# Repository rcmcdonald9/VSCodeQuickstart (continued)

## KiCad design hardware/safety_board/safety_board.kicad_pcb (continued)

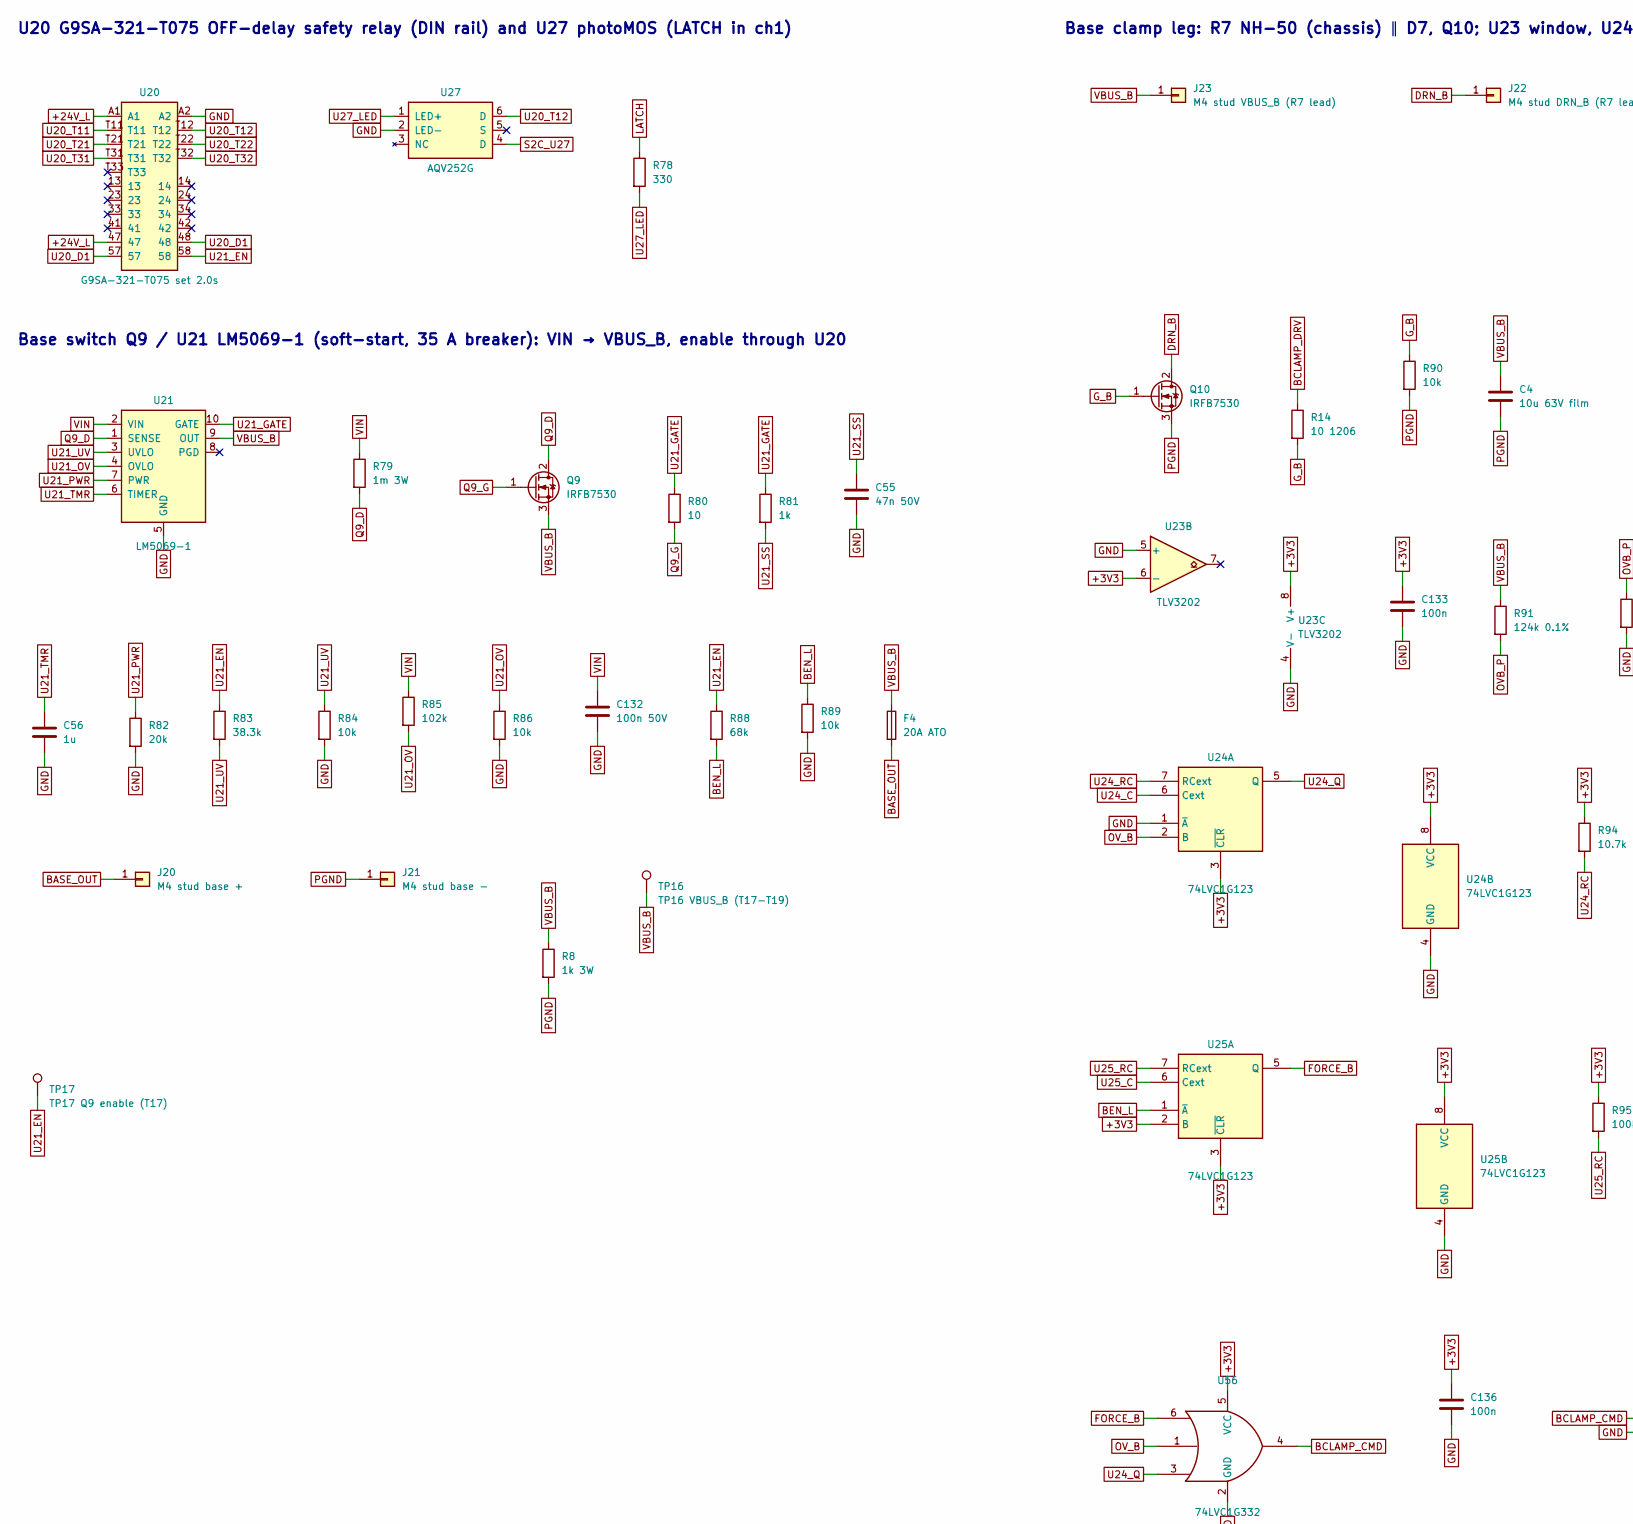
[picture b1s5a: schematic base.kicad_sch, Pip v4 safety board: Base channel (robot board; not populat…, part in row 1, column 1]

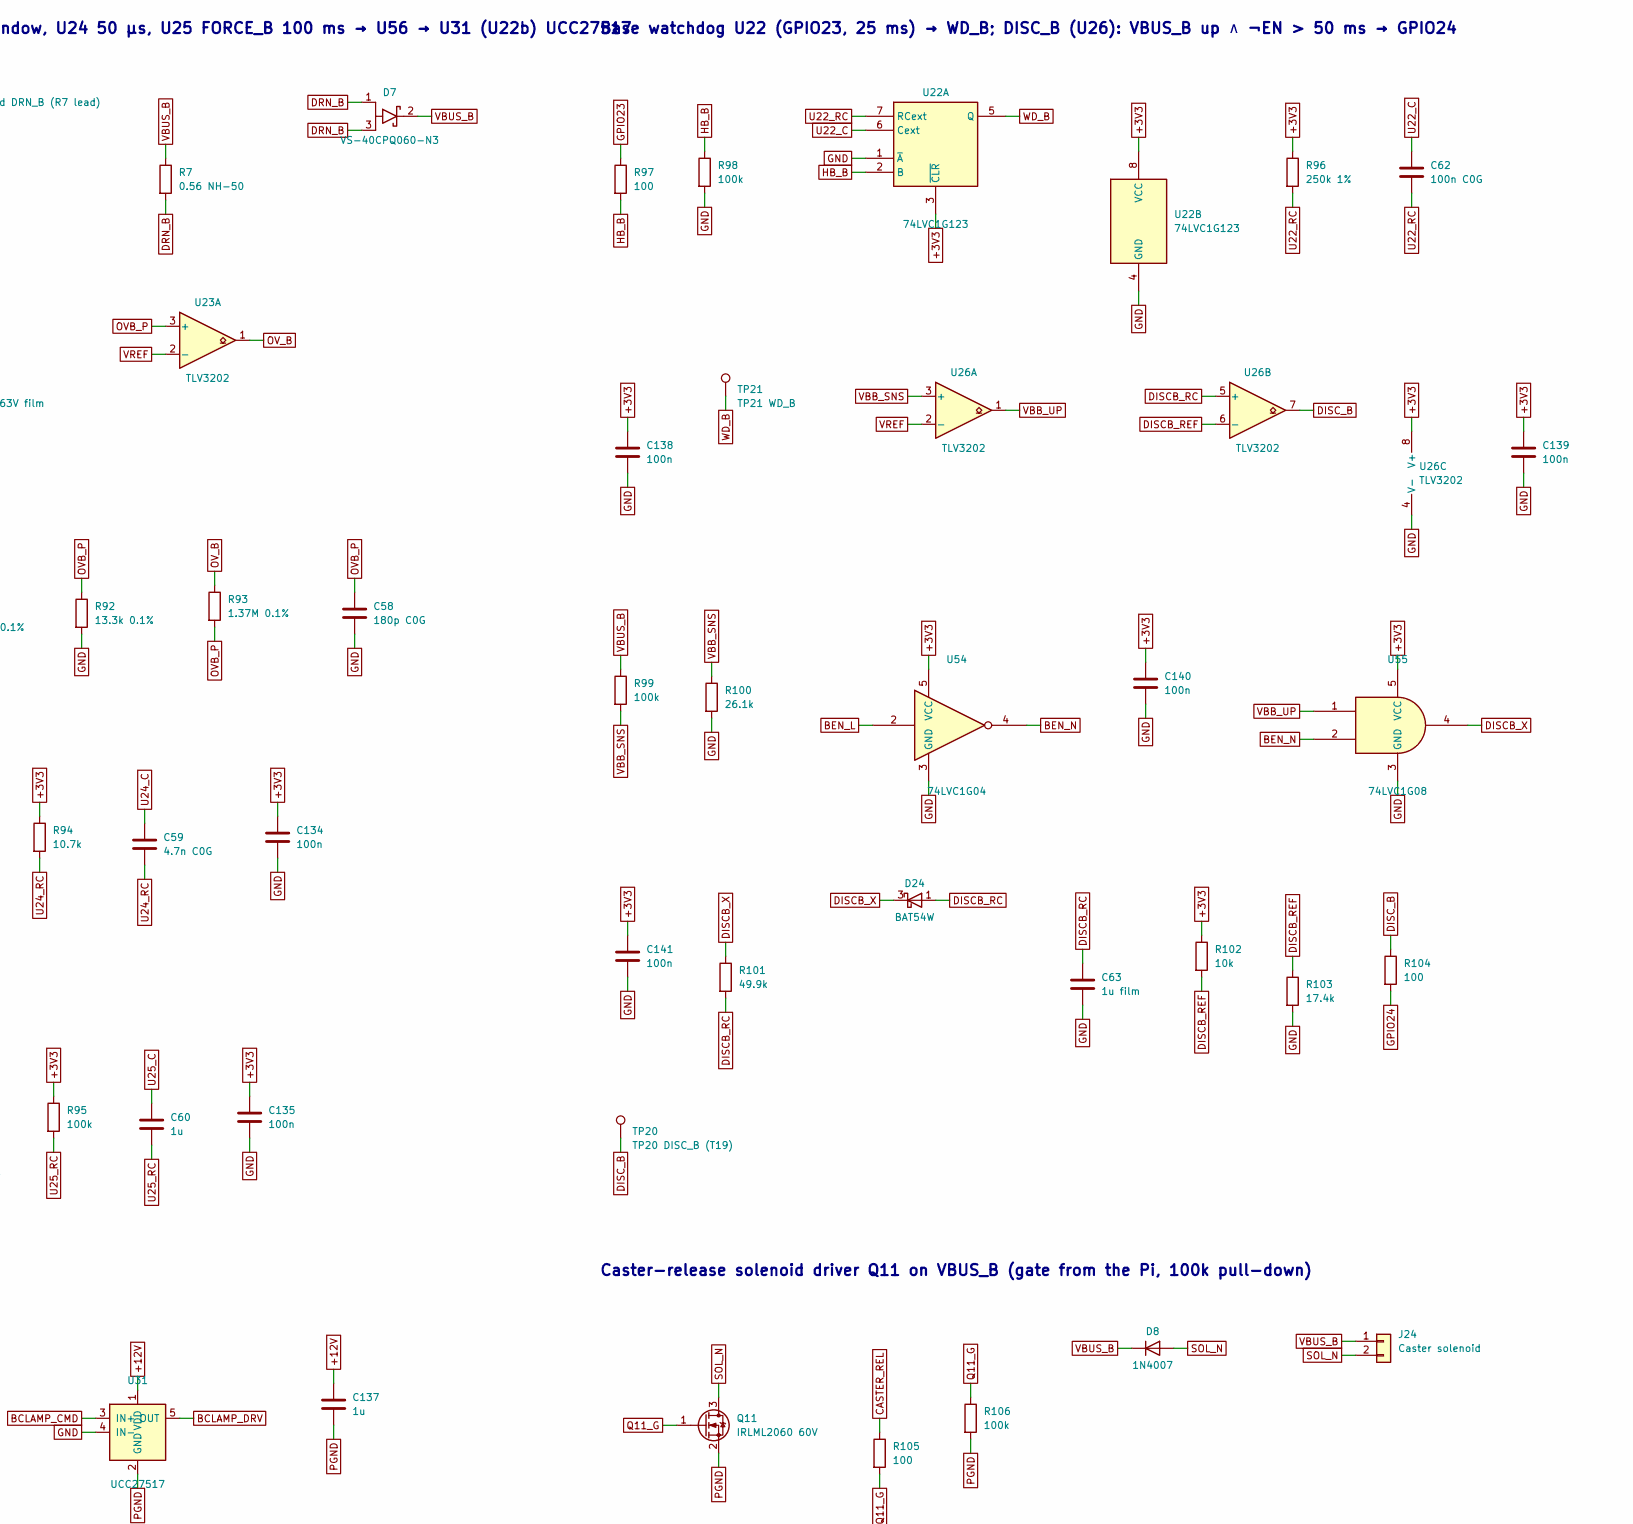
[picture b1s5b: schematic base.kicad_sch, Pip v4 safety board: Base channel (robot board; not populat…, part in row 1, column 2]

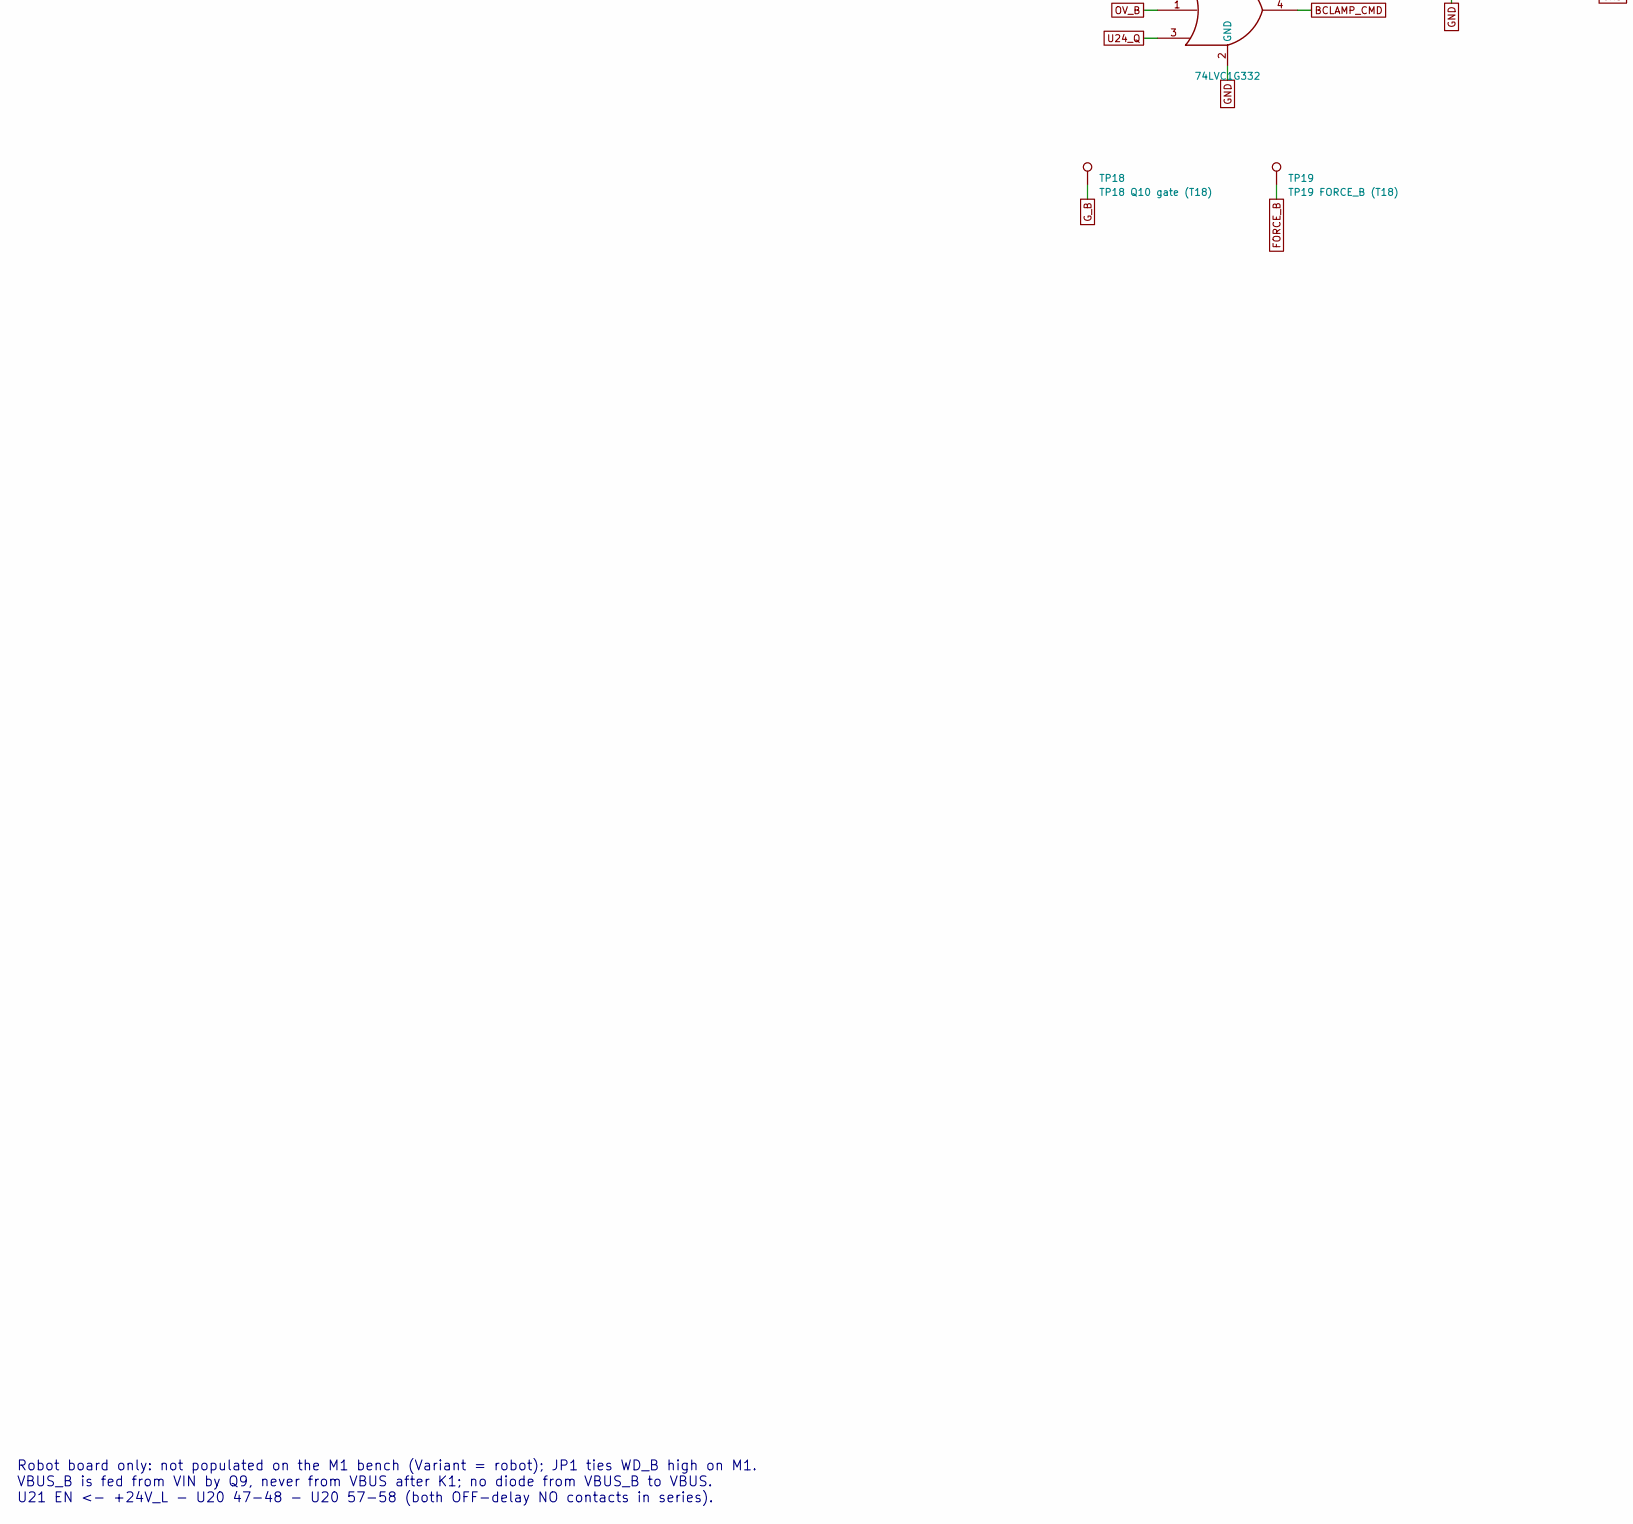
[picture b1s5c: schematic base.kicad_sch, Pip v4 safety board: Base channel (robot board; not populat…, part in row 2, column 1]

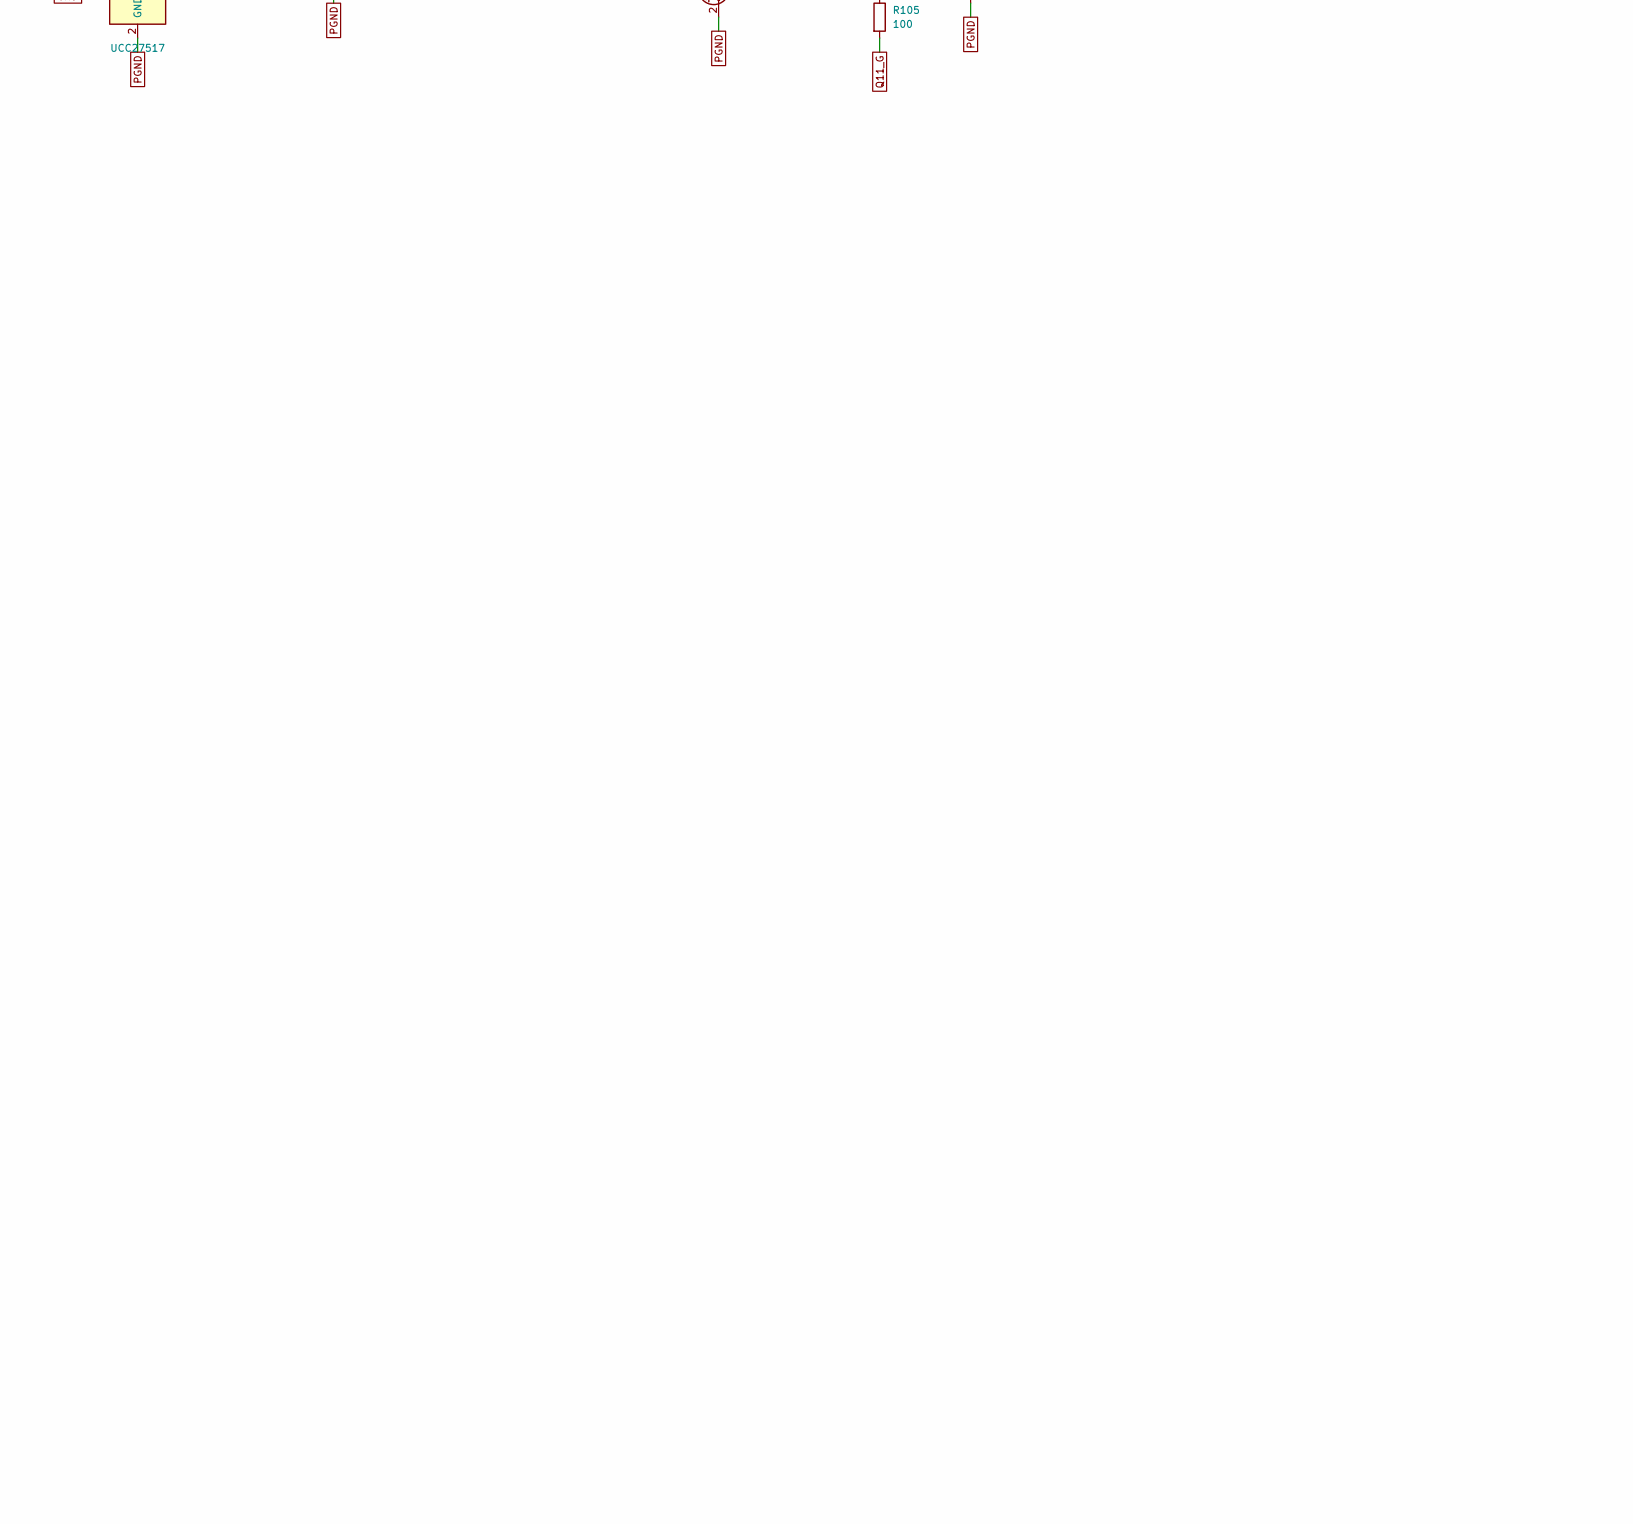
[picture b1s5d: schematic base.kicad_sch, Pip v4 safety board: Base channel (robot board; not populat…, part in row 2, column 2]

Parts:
C4: 10u 63V film; C_Rect_L31.5mm_W11.0mm_P27.50mm_MKS4
C55: 47n 50V; C_0603_1608Metric
C56, C60: 1u; C_1206_3216Metric
C58: 180p C0G; C_0603_1608Metric
C59: 4.7n C0G; C_0603_1608Metric
C62: 100n C0G; C_0603_1608Metric
C63: 1u film; C_1206_3216Metric
C132: 100n 50V; C_0603_1608Metric
C133, C134, C135, C136, C138, C139, C140, C141: 100n; C_0603_1608Metric
C137: 1u; C_0603_1608Metric
D7: VS-40CPQ060-N3; TO-247-3_Vertical
D8: 1N4007; D_DO-41_SOD81_P10.16mm_Horizontal
D24: BAT54W; SOT-323_SC-70
F4: 20A ATO; Fuseholder_Blade_ATO_Littelfuse_Pudenz_2_Pin
J20: M4 stud base +; MountingHole_4.3mm_M4_Pad_Via
J21: M4 stud base -; MountingHole_4.3mm_M4_Pad_Via
J22: M4 stud DRN_B (R7 lead); MountingHole_4.3mm_M4_Pad_Via
J23: M4 stud VBUS_B (R7 lead); MountingHole_4.3mm_M4_Pad_Via
J24: Caster solenoid; JST_VH_B2P-VH_1x02_P3.96mm_Vertical
Q9, Q10: IRFB7530; TO-220-3_Vertical
Q11: IRLML2060 60V; SOT-23
R7: 0.56 NH-50
R8: 1k 3W; R_Axial_Power_L20.0mm_W6.4mm_P22.40mm
R14: 10 1206; R_1206_3216Metric
R78: 330; R_0603_1608Metric
R79: 1m 3W; R_2512_6332Metric
R80: 10; R_0603_1608Metric
R81: 1k; R_0603_1608Metric
R82: 20k; R_0603_1608Metric
R83: 38.3k; R_0603_1608Metric
R84, R86, R89, R90, R102: 10k; R_0603_1608Metric
R85: 102k; R_0603_1608Metric
R88: 68k; R_0603_1608Metric
R91: 124k 0.1%; R_0603_1608Metric
R92: 13.3k 0.1%; R_0603_1608Metric
R93: 1.37M 0.1%; R_0603_1608Metric
R94: 10.7k; R_0603_1608Metric
R95, R98, R99, R106: 100k; R_0603_1608Metric
R96: 250k 1%; R_0603_1608Metric
R97, R104, R105: 100; R_0603_1608Metric
R100: 26.1k; R_0603_1608Metric
R101: 49.9k; R_0603_1608Metric
R103: 17.4k; R_0603_1608Metric
TP16: TP16 VBUS_B (T17-T19); TestPoint_Keystone_5005-5009_Compact
TP17: TP17 Q9 enable (T17); TestPoint_Keystone_5005-5009_Compact
TP18: TP18 Q10 gate (T18); TestPoint_Keystone_5005-5009_Compact
TP19: TP19 FORCE_B (T18); TestPoint_Keystone_5005-5009_Compact
TP20: TP20 DISC_B (T19); TestPoint_Keystone_5005-5009_Compact
TP21: TP21 WD_B; TestPoint_Keystone_5005-5009_Compact
U20: G9SA-321-T075 set 2.0s
U21: LM5069-1; MSOP-10_3x3mm_P0.5mm
U22, U24, U25: 74LVC1G123; VSSOP-8_2.3x2mm_P0.5mm
U23, U26: TLV3202; SOIC-8_3.9x4.9mm_P1.27mm
U27: AQV252G; DIP-6_W7.62mm
U31: UCC27517; SOT-23-5
U54: 74LVC1G04; SOT-23-5
U55: 74LVC1G08; SOT-23-5
U56: 74LVC1G332; SOT-23-6

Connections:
+3V3: C133.1, C134.1, C135.1, C136.1, C138.1, C139.1, C140.1, C141.1, R94.1, R95.1, R96.1, R102.1, U22.3 (~CLR), U22.8 (VCC), U23.6 (-), U23.8 (V+), U24.3 (~CLR), U24.8 (VCC), U25.2 (B), U25.3 (~CLR), U25.8 (VCC), U26.8 (V+), U54.5 (VCC), U55.5 (VCC), U56.5 (VCC); also elsewhere on the board
+12V: C137.1, U31.1 (VDD); also elsewhere on the board
BASE_OUT: F4.2, J20.1
BCLAMP_CMD: U31.3 (IN+), U56.4
BCLAMP_DRV: R14.1, U31.5 (OUT)
BEN_L: R88.2, R89.1, U25.1 (~A), U54.2
BEN_N: U54.4, U55.2
CASTER_REL: R105.1; also elsewhere on the board
DISCB_RC: C63.1, D24.1 (A), R101.2, U26.5 (+)
DISCB_REF: R102.2, R103.1, U26.6 (-)
DISCB_X: D24.3 (K), R101.1, U55.4
DISC_B: R104.1, TP20.1, U26.7
DRN_B: D7.1 (A), D7.3 (A), J22.1, Q10.2 (D), R7.2
FORCE_B: TP19.1, U25.5 (Q), U56.6
GND: C55.2, C56.2, C58.2, C63.2, C132.2, C133.2, C134.2, C135.2, C136.2, C138.2, C139.2, C140.2, C141.2, R82.2, R84.2, R86.2, R89.2, R92.2, R98.2, R100.2, R103.2, U20.A2, U21.5 (GND), U22.1 (~A), U22.4 (GND), U23.4 (V-), U23.5 (+), U24.1 (~A), U24.4 (GND), U25.4 (GND), U26.4 (V-), U27.2 (LED-), U31.4 (IN-), U54.3 (GND), U55.3 (GND), U56.2 (GND); also elsewhere on the board
GPIO23: R97.1; also elsewhere on the board
GPIO24: R104.2; also elsewhere on the board
G_B: Q10.1 (G), R14.2, R90.1, TP18.1
HB_B: R97.2, R98.1, U22.2 (B)
LATCH: R78.1; also elsewhere on the board
unnamed: U20.47, U20.A1
unnamed: U20.48, U20.57
OVB_P: C58.1, R91.2, R92.1, R93.2, U23.3 (+)
OV_B: R93.1, U23.1, U24.2 (B), U56.1
PGND: C4.2, C137.2, J21.1, Q10.3 (S), Q11.2 (S), R8.2, R90.2, R106.2, U31.2 (GND); also elsewhere on the board
Q9_D: Q9.2 (D), R79.2, U21.1 (SENSE)
Q9_G: Q9.1 (G), R80.2
Q11_G: Q11.1 (G), R105.2, R106.1
S2C_U27: U27.4 (D); also elsewhere on the board
SOL_N: D8.2 (A), J24.2, Q11.3 (D)
U20_T12: U20.T12, U27.6 (D); also elsewhere on the board
U21_EN: R83.1, R88.1, TP17.1, U20.58; also elsewhere on the board
U21_GATE: R80.1, R81.1, U21.10 (GATE)
U21_OV: R85.2, R86.1, U21.4 (OVLO)
U21_PWR: R82.1, U21.7 (PWR)
U21_SS: C55.1, R81.2
U21_TMR: C56.1, U21.6 (TIMER)
U21_UV: R83.2, R84.1, U21.3 (UVLO)
U22_C: C62.1, U22.6 (Cext)
U22_RC: C62.2, R96.2, U22.7 (RCext)
U24_C: C59.1, U24.6 (Cext)
U24_Q: U24.5 (Q), U56.3
U24_RC: C59.2, R94.2, U24.7 (RCext)
U25_C: C60.1, U25.6 (Cext)
U25_RC: C60.2, R95.2, U25.7 (RCext)
U27_LED: R78.2, U27.1 (LED+)
VBB_SNS: R99.2, R100.1, U26.3 (+)
VBB_UP: U26.1, U55.1
VBUS_B: C4.1, D7.2 (K), D8.1 (K), F4.1, J23.1, J24.1, Q9.3 (S), R7.1, R8.1, R91.1, R99.1, TP16.1, U21.9 (OUT)
VIN: C132.1, R79.1, R85.1, U21.2 (VIN); also elsewhere on the board
VREF: U23.2 (-), U26.2 (-); also elsewhere on the board
WD_B: TP21.1, U22.5 (Q); also elsewhere on the board

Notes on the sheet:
U20 G9SA-321-T075 OFF-delay safety relay (DIN rail) and U27 photoMOS (LATCH in ch1)
Base switch Q9 / U21 LM5069-1 (soft-start, 35 A breaker): VIN → VBUS_B, enable through U20
Base clamp leg: R7 NH-50 (chassis) ∥ D7, Q10; U23 window, U24 50 µs, U25 FORCE_B 100 ms → U56 → U31 (U22b) UCC27517
Base watchdog U22 (GPIO23, 25 ms) → WD_B; DISC_B (U26): VBUS_B up ∧ ¬EN > 50 ms → GPIO24
Caster-release solenoid driver Q11 on VBUS_B (gate from the Pi, 100k pull-down)
Robot board only: not populated on the M1 bench (Variant = robot); JP1 ties WD_B high on M1. VBUS_B is fed from VIN by Q9, never from VBUS after K1; no diode from VBUS_B to VBUS. U21 EN <- +24V_L - U20 47-48 - U20 57-58 (both OFF-delay NO contacts in series).

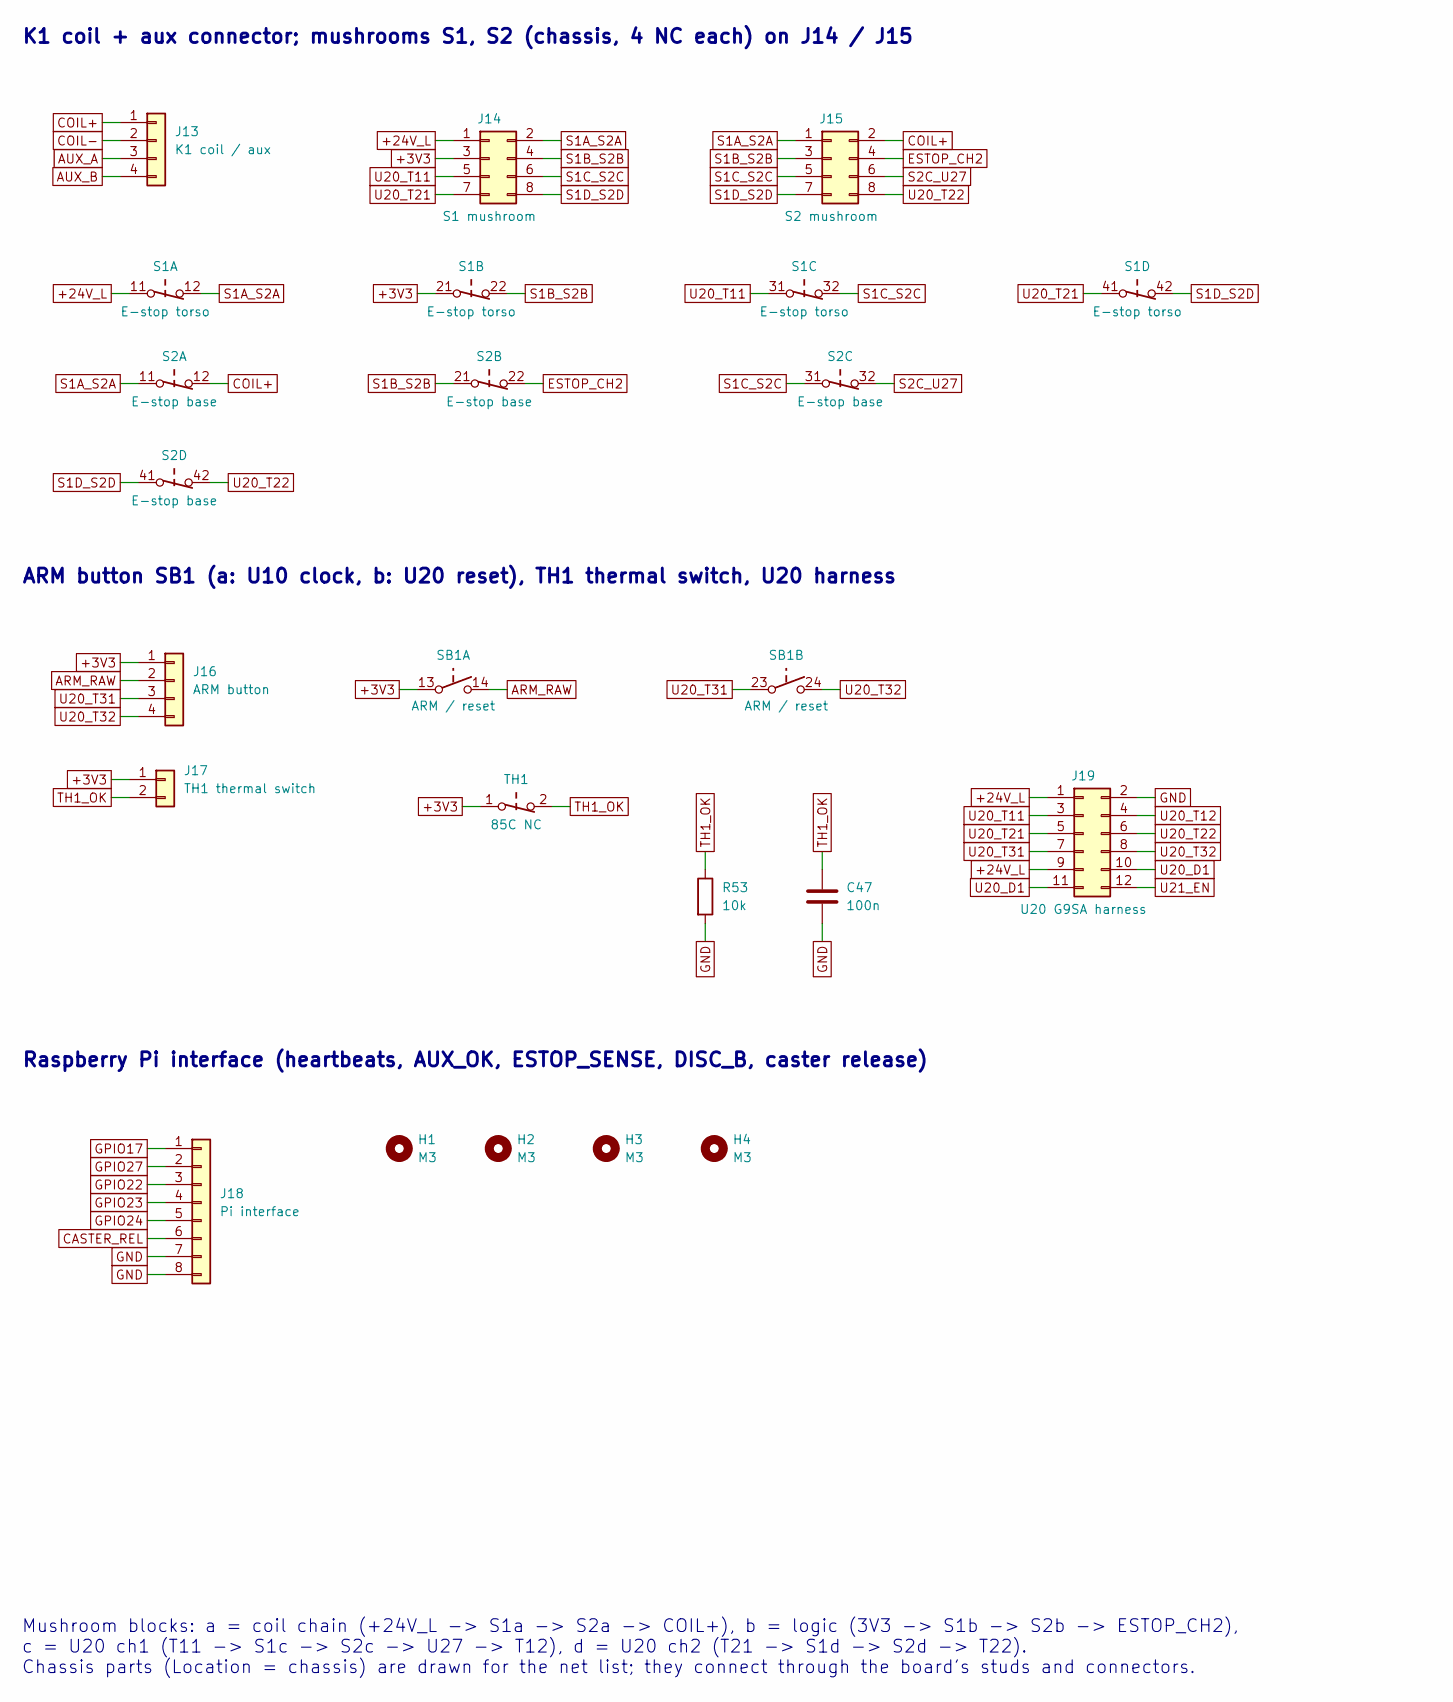
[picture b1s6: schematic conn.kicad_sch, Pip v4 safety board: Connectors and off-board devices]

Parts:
C47: 100n; C_0603_1608Metric
H1, H2, H3, H4: M3; MountingHole_3.2mm_M3
J13: K1 coil / aux; JST_VH_B4P-VH_1x04_P3.96mm_Vertical
J14: S1 mushroom; Molex_Micro-Fit_3.0_43045-0800_2x04_P3.00mm_Horizontal
J15: S2 mushroom; Molex_Micro-Fit_3.0_43045-0800_2x04_P3.00mm_Horizontal
J16: ARM button; Molex_Micro-Fit_3.0_43650-0400_1x04_P3.00mm_Horizontal
J17: TH1 thermal switch; JST_VH_B2P-VH_1x02_P3.96mm_Vertical
J18: Pi interface; JST_PH_B8B-PH-K_1x08_P2.00mm_Vertical
J19: U20 G9SA harness; Molex_Micro-Fit_3.0_43045-1200_2x06_P3.00mm_Horizontal
R53: 10k; R_0603_1608Metric
S1: E-stop torso
S2: E-stop base
SB1: ARM / reset
TH1: 85C NC

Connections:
+3V3: J14.3, J16.1, J17.1, S1.21, SB1.13, TH1.1; also elsewhere on the board
+24V_L: J14.1, J19.1, J19.9, S1.11; also elsewhere on the board
ARM_RAW: J16.2, SB1.14; also elsewhere on the board
AUX_A: J13.3; also elsewhere on the board
AUX_B: J13.4; also elsewhere on the board
CASTER_REL: J18.6; also elsewhere on the board
COIL+: J13.1, J15.2, S2.12; also elsewhere on the board
COIL-: J13.2; also elsewhere on the board
ESTOP_CH2: J15.4, S2.22; also elsewhere on the board
GND: C47.2, J18.7, J18.8, J19.2, R53.2; also elsewhere on the board
GPIO17: J18.1; also elsewhere on the board
GPIO22: J18.3; also elsewhere on the board
GPIO23: J18.4; also elsewhere on the board
GPIO24: J18.5; also elsewhere on the board
GPIO27: J18.2; also elsewhere on the board
S1A_S2A: J14.2, J15.1, S1.12, S2.11
S1B_S2B: J14.4, J15.3, S1.22, S2.21
S1C_S2C: J14.6, J15.5, S1.32, S2.31
S1D_S2D: J14.8, J15.7, S1.42, S2.41
S2C_U27: J15.6, S2.32; also elsewhere on the board
TH1_OK: C47.1, J17.2, R53.1, TH1.2; also elsewhere on the board
U20_D1: J19.10, J19.11
U20_T11: J14.5, J19.3, S1.31
U20_T12: J19.4; also elsewhere on the board
U20_T21: J14.7, J19.5, S1.41
U20_T22: J15.8, J19.6, S2.42
U20_T31: J16.3, J19.7, SB1.23
U20_T32: J16.4, J19.8, SB1.24
U21_EN: J19.12; also elsewhere on the board

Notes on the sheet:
K1 coil + aux connector; mushrooms S1, S2 (chassis, 4 NC each) on J14 / J15
ARM button SB1 (a: U10 clock, b: U20 reset), TH1 thermal switch, U20 harness
Raspberry Pi interface (heartbeats, AUX_OK, ESTOP_SENSE, DISC_B, caster release)
Mushroom blocks: a = coil chain (+24V_L -> S1a -> S2a -> COIL+), b = logic (3V3 -> S1b -> S2b -> ESTOP_CH2), c = U20 ch1 (T11 -> S1c -> S2c -> U27 -> T12), d = U20 ch2 (T21 -> S1d -> S2d -> T22). Chassis parts (Location = chassis) are drawn for the net list; they connect through the board's studs a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

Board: 2 copper layers, 288 parts (0 on the bottom side), 152 nets, no tracks yet.
